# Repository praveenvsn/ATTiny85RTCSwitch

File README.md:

# ATTiny85RTCSwitch
This project contains Eagle Libraries and Source code for an ATTiny85 and DS1307 based switch to automatically control an AC light through MOC3041

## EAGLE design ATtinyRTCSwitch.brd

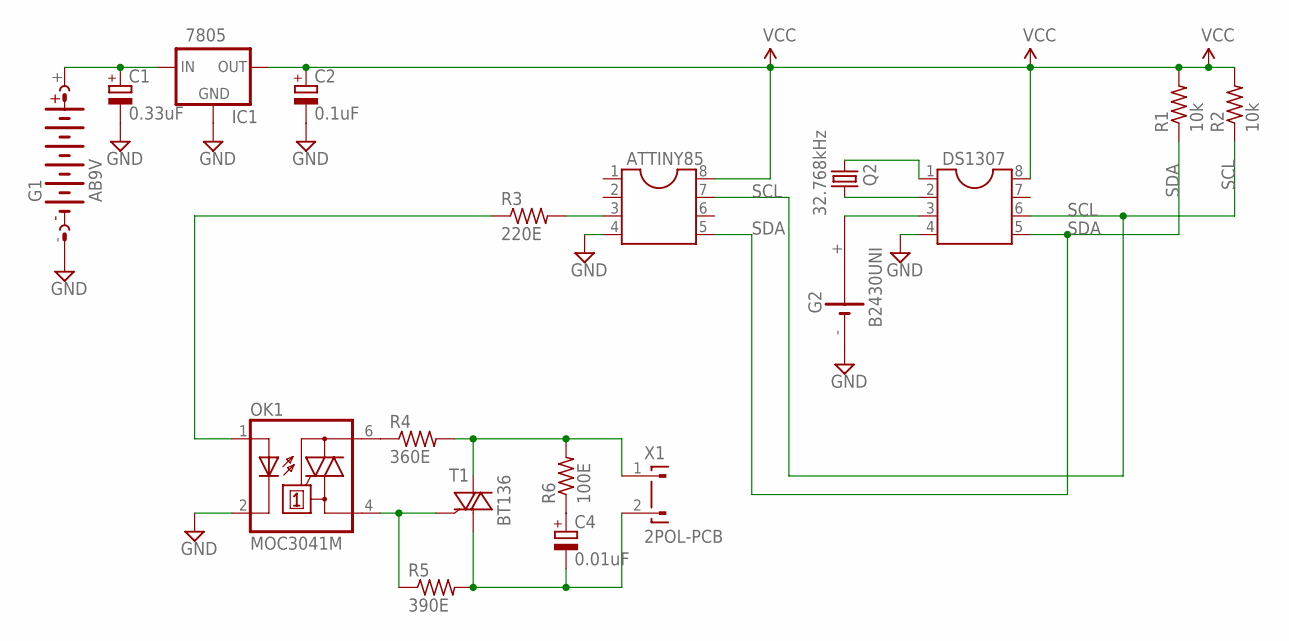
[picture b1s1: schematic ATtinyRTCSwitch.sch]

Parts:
ATTINY85: DIL8; DIL08
C1: 0.33uF; E2,5-5
C2: 0.1uF; E2,5-5
C4: 0.01uF; E2,5-5
DS1307: DIL8; DIL08
G1: AB9V
G2: B2430UNI
IC1: 7805; 78XXL
OK1: MOC3041M; DIL06
Q2: 32.768kHz; TC26H
R1, R2: 10k; 0204/7
R3: 220E; 0204/7
R4: 360E; 0204/7
R5: 390E; 0204/7
R6: 100E; 0204/7
T1: BT136; TO220AB
X1: 2POL-PCB

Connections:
GND: ATTINY85.4, C1.-, C2.-, DS1307.4, G1.-, G2.-, IC1.GND, OK1.2 (C)
unnamed: OK1.4 (A1), R5.1, T1.3 (G)
unnamed: DS1307.1, Q2.2
unnamed: DS1307.2, Q2.1
unnamed: C1.+, G1.+, IC1.IN
unnamed: DS1307.3, G2.+
unnamed: C4.-, R5.2, T1.1 (A1), X1.2
unnamed: R4.2, R6.2, T1.2 (A2), X1.1
unnamed: OK1.6 (A2), R4.1
unnamed: C4.+, R6.1
unnamed: ATTINY85.3, R3.2
SCL: ATTINY85.7, DS1307.6, R2.1
SDA: ATTINY85.5, DS1307.5, R1.1
SWITCH_ON: OK1.1 (A), R3.1
VCC: ATTINY85.8, C2.+, DS1307.8, IC1.OUT, R1.2, R2.2

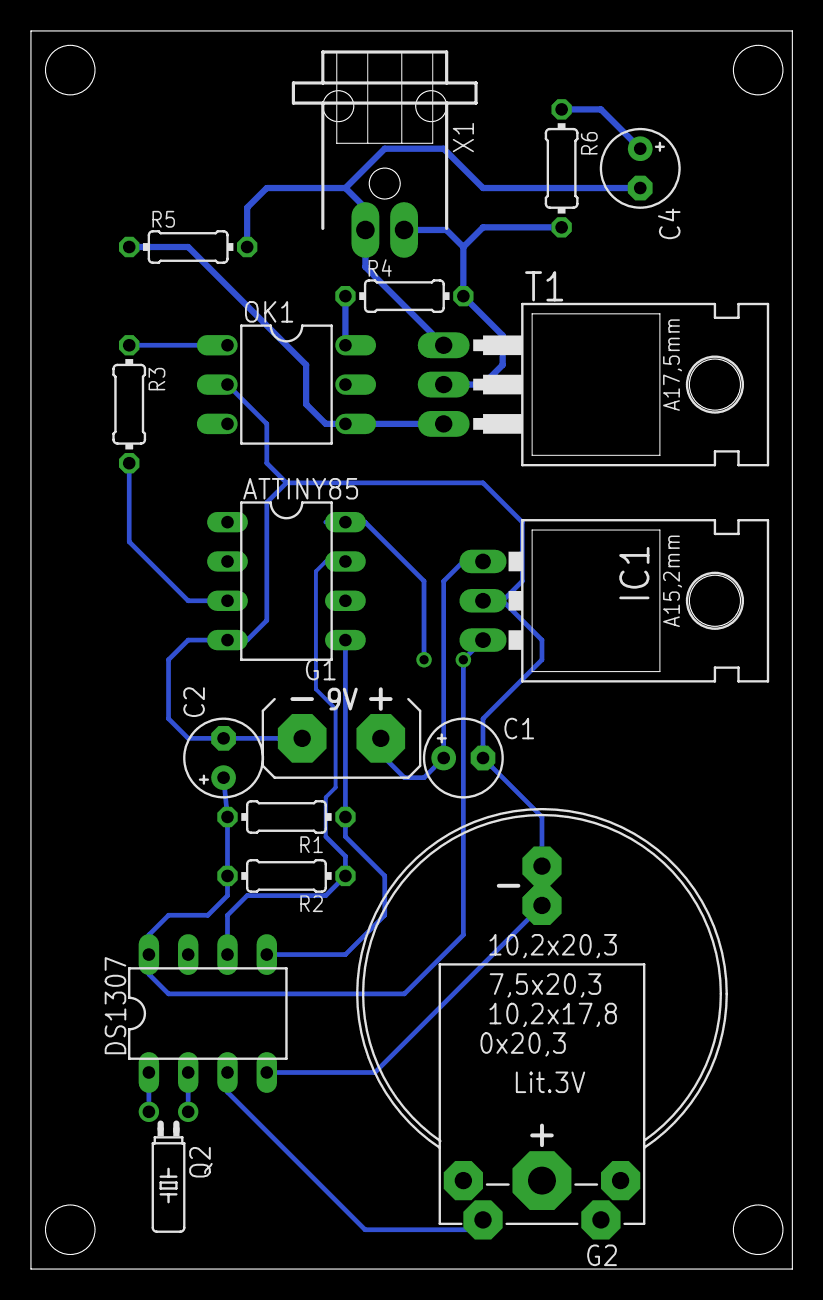
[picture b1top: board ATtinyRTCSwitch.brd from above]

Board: 2 copper layers, 49.2 x 80.0 mm, 18 parts (0 on the bottom side), 15 nets.

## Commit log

2016-03-28 Added files via upload
